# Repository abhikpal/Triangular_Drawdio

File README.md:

# Triangular Drawdio!

## What is it?

It is a remix of [Jay Silver's original Drawdio](http://web.media.mit.edu/~silver/drawdio/), the main difference being the new triangular shape. It is designed to be printed on a single side copper laminate and uses two coin cells as the primary power source.

## What can I do with it?

Anything! Just don't blame me if you happen blow things up. Feel free to hack it, or make it your own.

## Licensing Information

I don't have any proper licence for this thing. What this basically means that if something goes wrong (like aliens coming and abducting you), you are responsible. Use whatever that is there in this repo at your own risk.

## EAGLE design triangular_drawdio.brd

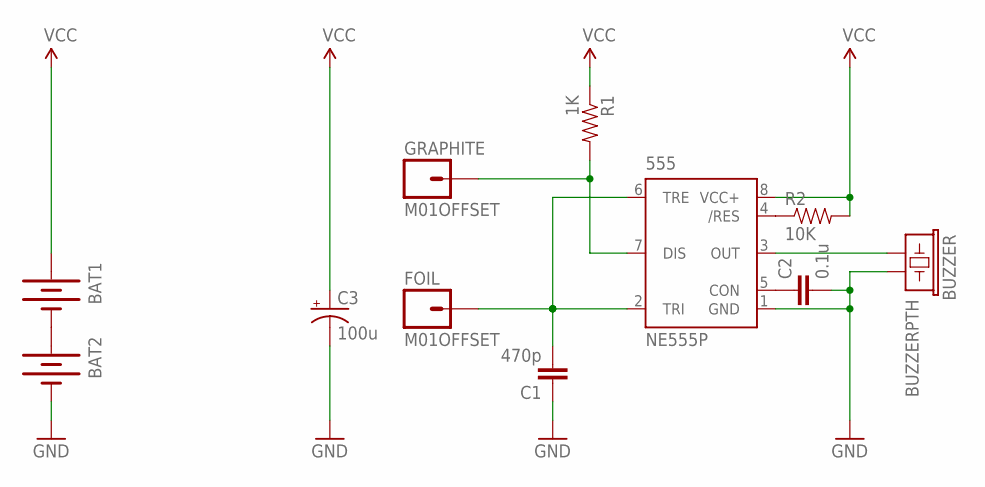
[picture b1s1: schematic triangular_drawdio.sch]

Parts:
555: NE555P; DIL-08
BAT1, BAT2: BATTERY20PTH; BATTCOM_20MM_PTH
BUZZER: BUZZERPTH; BUZZER-12MM
C1: 470p; CAP-PTH-SMALL2
C2: 0.1u; CAP-PTH-SMALL2
C3: 100u; CPOL-RADIAL-10UF-25V
FOIL: M01OFFSET; 1X01_OFFSET
GRAPHITE: M01OFFSET; 1X01_OFFSET
R1: 1K; AXIAL-0.4
R2: 10K; AXIAL-0.4

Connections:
GND: 555.1 (GND), BAT2.2 (-), BUZZER.- (2), C1.1, C2.2, C3.2 (-)
unnamed: 555.5 (CON), C2.1
unnamed: 555.3 (OUT), BUZZER.+ (1)
unnamed: 555.4 (/RES), R2.P$1 (1)
unnamed: 555.7 (DIS), GRAPHITE.1, R1.P$2 (2)
unnamed: 555.2 (TRI), 555.6 (TRE), C1.2, FOIL.1
VCC: 555.8 (VCC+), BAT1.1 (+), C3.1 (+), R1.P$1 (1), R2.P$2 (2)
V_ALT: BAT1.2 (-), BAT2.1 (+)

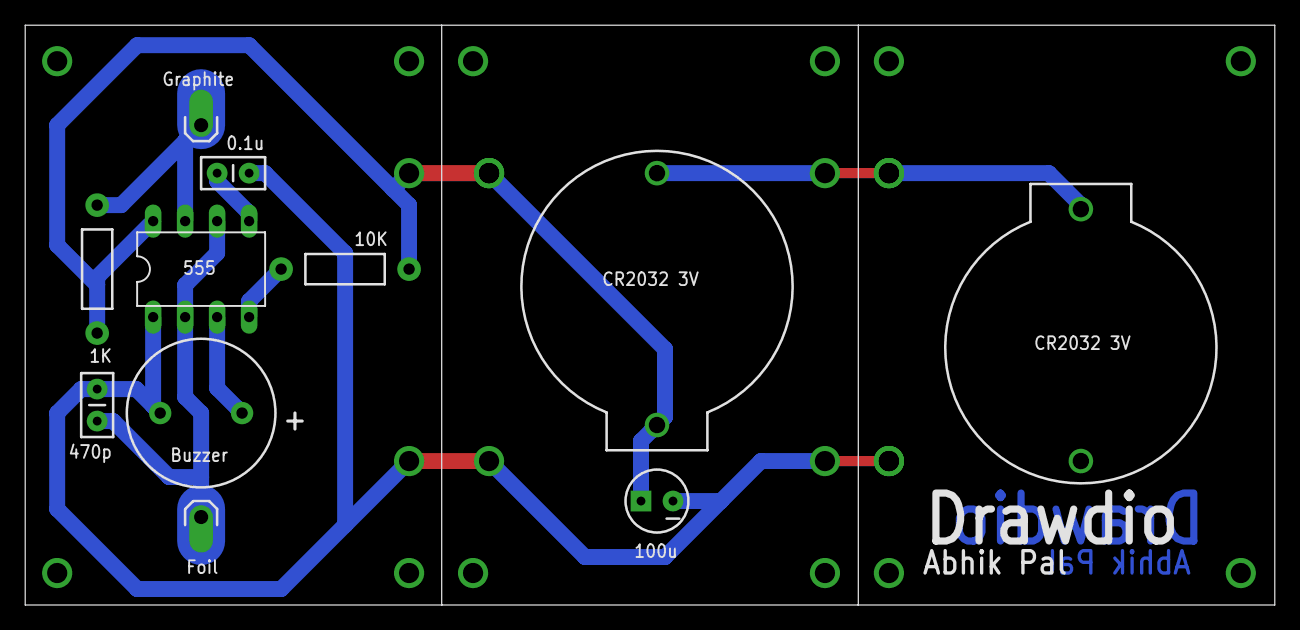
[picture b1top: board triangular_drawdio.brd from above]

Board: 2 copper layers, 99.2 x 46.0 mm, 11 parts (0 on the bottom side), 8 nets.

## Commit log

2014-04-25 Initial Commit
    First version of the triangular drawdio.
2015-02-09 Added a README

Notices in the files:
parts and their libraries:
SparkFun-Resistors: Licensing: CC v3.0 Share-Alike You are welcome to use this library for commercial purposes.
